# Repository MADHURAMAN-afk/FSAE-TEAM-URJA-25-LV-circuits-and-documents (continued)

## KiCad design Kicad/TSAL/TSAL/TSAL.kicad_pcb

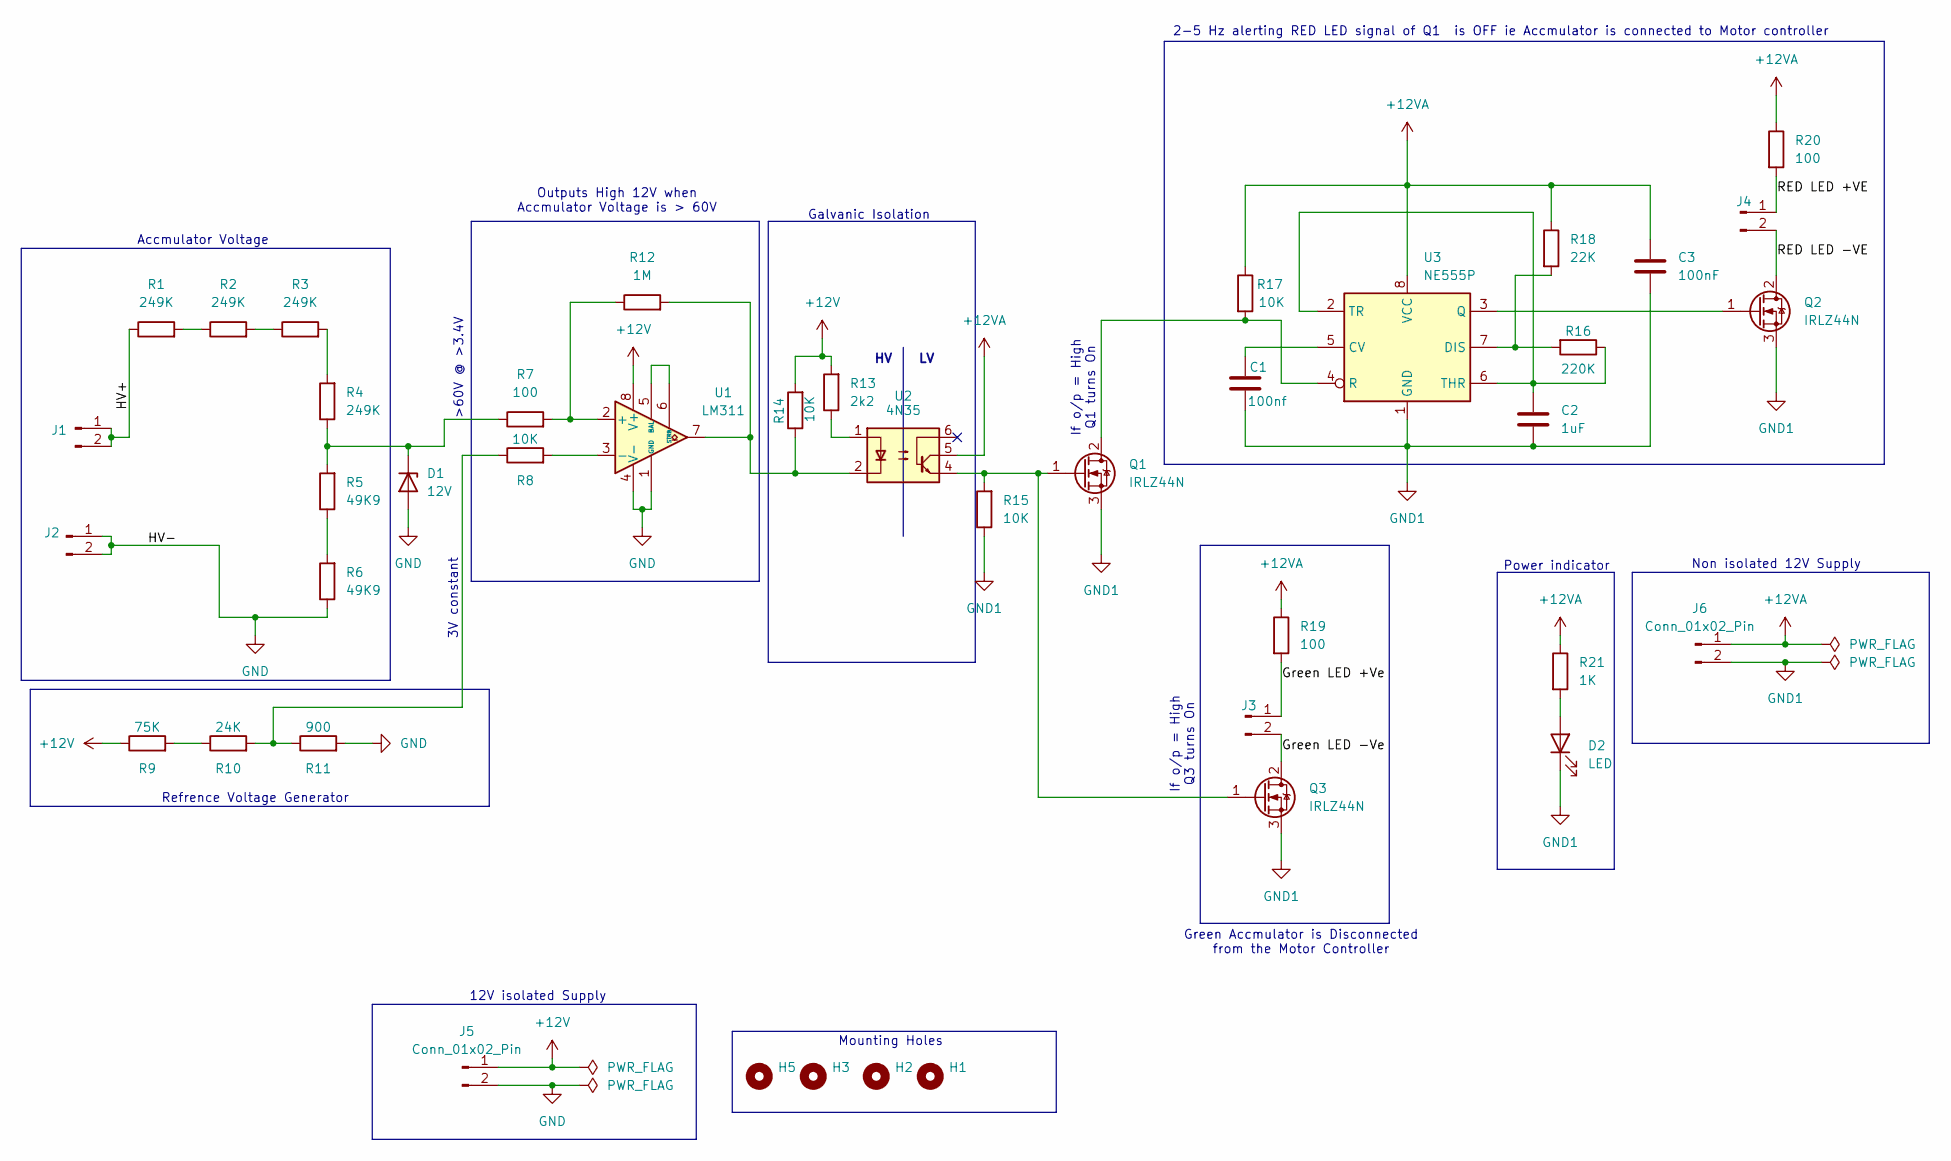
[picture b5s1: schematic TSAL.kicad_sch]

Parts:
C1: 100nf; CP_Radial_D10.0mm_P5.00mm
C2: 1uF; CP_Radial_D10.0mm_P5.00mm
C3: 100nF; CP_Radial_D10.0mm_P5.00mm
D1: 12V; D_A-405_P7.62mm_Horizontal
D2: LED; LED_D5.0mm
H1, H2, H3, H5: MountingHole; MountingHole_4.3mm_M4
J1: HV +; TerminalBlock_Phoenix_MKDS-1,5-2-5.08_1x02_P5.08mm_Horizont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
J2, J3, J4, J5, J6: Conn_01x02_Pin; TerminalBlock_Phoenix_MKDS-1,5-2-5.08_1x02_P5.08mm_Horizont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
Q1, Q2, Q3: IRLZ44N; TO-220-3_Vertical
R1, R2, R3, R4: 249K; R_Axial_DIN0207_L6.3mm_D2.5mm_P7.62mm_Horizontal
R5, R6: 49K9; R_Axial_DIN0207_L6.3mm_D2.5mm_P7.62mm_Horizontal
R7, R19, R20: 100; R_Axial_DIN0207_L6.3mm_D2.5mm_P7.62mm_Horizontal
R8, R14, R15, R17: 10K; R_Axial_DIN0207_L6.3mm_D2.5mm_P7.62mm_Horizontal
R9: 75K; R_Axial_DIN0207_L6.3mm_D2.5mm_P7.62mm_Horizontal
R10: 24K; R_Axial_DIN0207_L6.3mm_D2.5mm_P7.62mm_Horizontal
R11: 900; R_Axial_DIN0207_L6.3mm_D2.5mm_P7.62mm_Horizontal
R12: 1M; R_Axial_DIN0207_L6.3mm_D2.5mm_P7.62mm_Horizontal
R13: 2k2; R_Axial_DIN0207_L6.3mm_D2.5mm_P7.62mm_Horizontal
R16: 220K; R_Axial_DIN0207_L6.3mm_D2.5mm_P7.62mm_Horizontal
R18: 22K; R_Axial_DIN0207_L6.3mm_D2.5mm_P7.62mm_Horizontal
R21: 1K; R_Axial_DIN0207_L6.3mm_D2.5mm_P7.62mm_Horizontal
U1: LM311; CERDIP-8_W7.62mm_SideBrazed
U2: 4N35; DIP-6_W7.62mm
U3: NE555P; DIP-8_W7.62mm

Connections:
+12V: J5.1, R9.1, R13.2, R14.2, U1.8 (V+)
+12VA: C3.1, J6.1, R17.1, R18.1, R19.1, R20.1, R21.1, U2.5, U3.8 (VCC)
/Green LED +Ve: J3.1, R19.2
/Green LED -Ve: J3.2, Q3.2 (D)
/RED LED +VE: J4.1, R20.2
/RED LED -VE: J4.2, Q2.2 (D)
GND1: C1.2, C2.2, C3.2, D2.1 (K), J6.2, Q1.3 (S), Q2.3 (S), Q3.3 (S), R15.1, U3.1 (GND)
HV +VE: J1.1, J1.2, R1.1
HV -VE: D1.2 (A), J2.1, J2.2, J5.2, R6.1, R11.2, U1.1 (GND), U1.4 (V-)
unnamed: D1.1 (K), R4.1, R5.2, R7.1
unnamed: D2.2 (A), R21.2
unnamed: Q1.2 (D), R17.2, U3.4 (R)
unnamed: Q1.1 (G), Q3.1 (G), R15.2, U2.4
unnamed: Q2.1 (G), U3.3 (Q)
unnamed: R1.2, R2.1
unnamed: R2.2, R3.1
unnamed: R3.2, R4.2
unnamed: R5.1, R6.2
unnamed: R9.2, R10.1
unnamed: R8.1, R10.2, R11.1
unnamed: R12.2, R14.1, U1.7, U2.2
unnamed: R13.1, U2.1
unnamed: R7.2, R12.1, U1.2 (+)
unnamed: R8.2, U1.3 (-)
unnamed: U1.5 (BAL), U1.6 (STRB)
unnamed: C1.1, U3.5 (CV)
unnamed: R16.2, R18.2, U3.7 (DIS)
unnamed: C2.1, R16.1, U3.2 (TR), U3.6 (THR)

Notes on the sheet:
2-5 Hz alerting RED LED signal of Q1 is OFF ie Accmulator is connected to Motor controller
>60V @ >3.4V
If o/p = High Q3 turns On
Accmulator Voltage
If o/p = High Q1 turns On
Outputs High 12V when Accmulator Voltage is > 60V
Galvanic Isolation
3V constant
Mounting Holes
Non isolated 12V Supply
Refrence Voltage Generator
Power indicator
12V isolated Supply
Green Accmulator is Disconnected from the Motor Controller

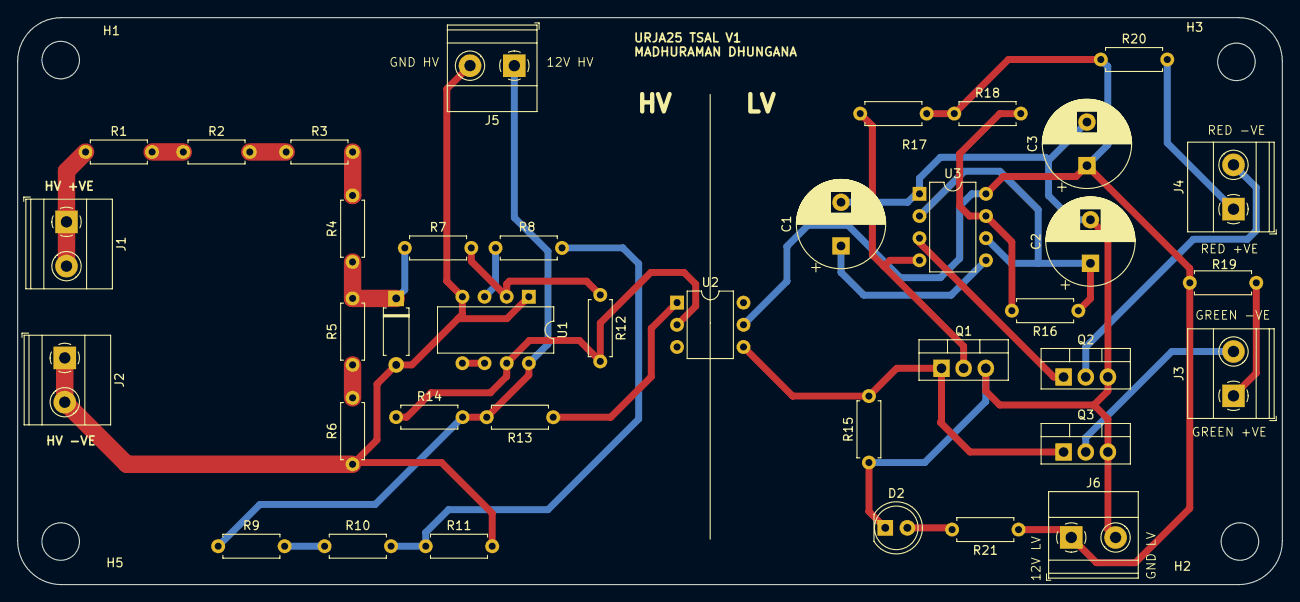
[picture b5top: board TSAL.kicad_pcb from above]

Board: 2 copper layers, 145.0 x 65.0 mm, 42 parts (0 on the bottom side), 28 nets.

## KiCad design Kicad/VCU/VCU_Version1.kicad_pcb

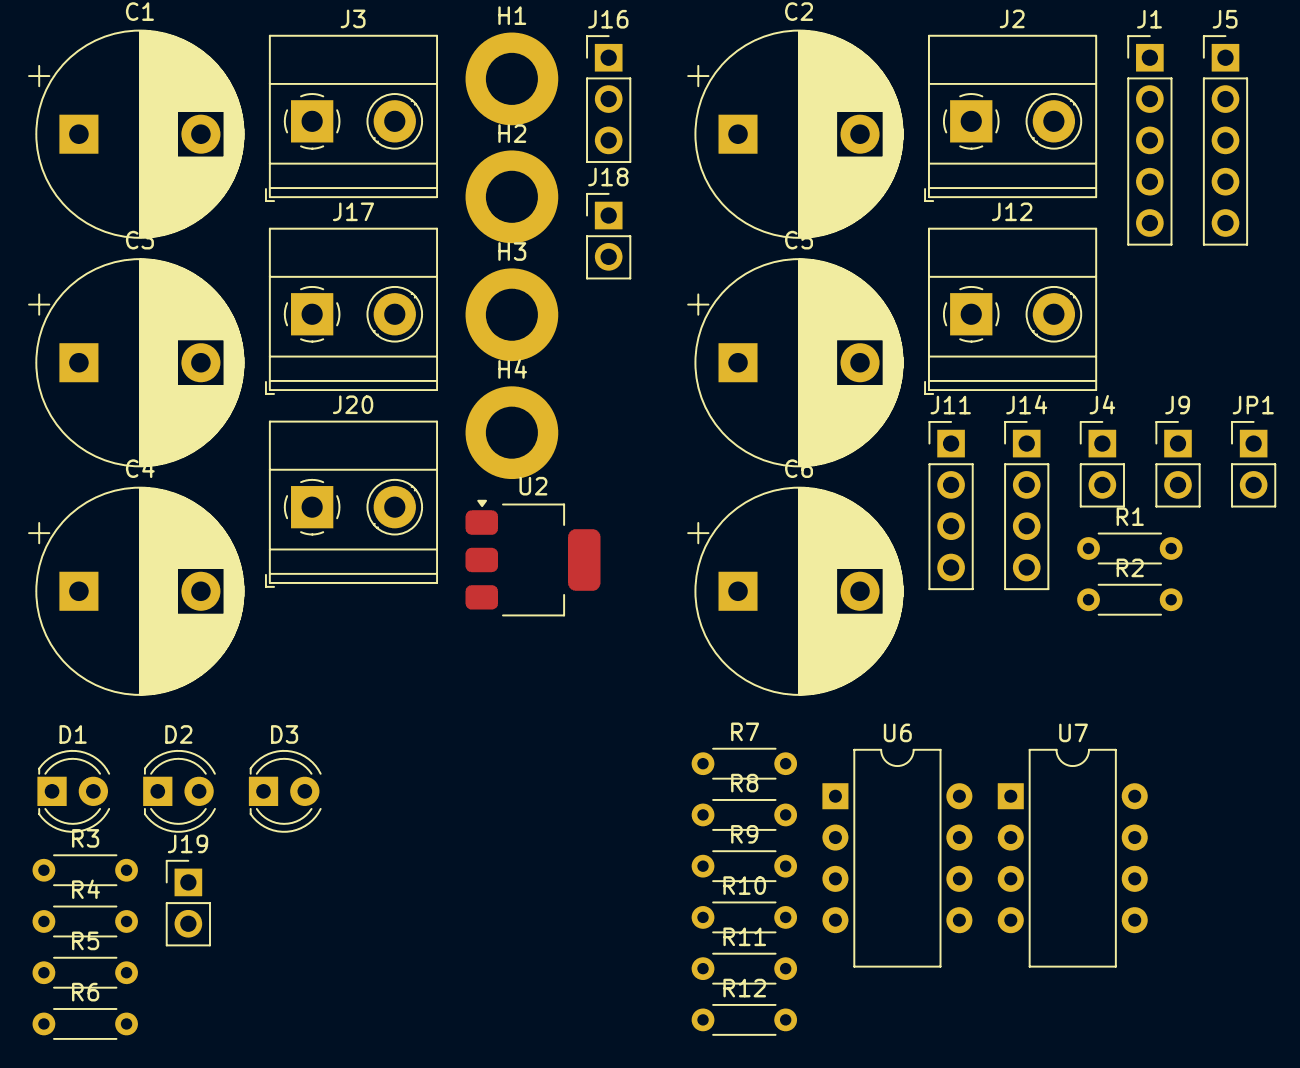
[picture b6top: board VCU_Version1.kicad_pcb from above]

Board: 2 copper layers, 43 parts (0 on the bottom side), 25 nets, no tracks yet.

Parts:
C1, C2, C3, C4, C5, C6: C; CP_Radial_D12.5mm_P7.50mm
D1, D2, D3: D; LED_D4.0mm
H1, H2, H3, H4: MountingHole_Pad; MountingHole_3.2mm_M3_ISO7380_Pad
J1, J5: Conn_01x05_Pin; PinHeader_1x05_P2.54mm_Vertical
J2, J12: Conn_01x02_Pin; TerminalBlock_Phoenix_MKDS-1,5-2-5.08_1x02_P5.08mm_Horizont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
J3, J17, J20: Screw_Terminal_01x02; TerminalBlock_Phoenix_MKDS-1,5-2-5.08_1x02_P5.08mm_Horizont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
J4, J9, J18, J19: Conn_01x02_Pin; PinHeader_1x02_P2.54mm_Vertical
J11, J14: Conn_01x04_Pin; PinHeader_1x04_P2.54mm_Vertical
J16: Conn_01x03_Pin; PinHeader_1x03_P2.54mm_Vertical
JP1: SolderJumper_2_Open; PinHeader_1x02_P2.54mm_Vertical
R1, R2: R_Small; R_Axial_DIN0204_L3.6mm_D1.6mm_P5.08mm_Horizontal
R3, R4, R5, R6, R7, R8, R9, R10, R11, R12: R; R_Axial_DIN0204_L3.6mm_D1.6mm_P5.08mm_Horizontal
U2: TLV76133DCY; SOT-223-3_TabPin2
U6, U7: LM741; CERDIP-8_W7.62mm_SideBrazed

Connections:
3V3: JP1.2 (B), R3.2
5V: C4.1, J20.2
+5V: C2.2, C6.1, J16.3
+5VA: C1.1, J17.2, U2.3 (VI)
+12V: J16.1, U6.7 (V+), U7.7 (V+)
Brake_Light_Digital: J5.4, R6.1
Free_GPIO1_AIR_Status: U7.2 (-), U7.6
Free_GPIO1_AIR_Status_In: J9.2, R10.1
GND: C2.1, C4.2, C5.1, C6.2, D1.1 (K), D2.1 (K), D3.1 (K), H1.1, H2.1, H3.1, H4.1, J3.1, J12.1, J20.1, R8.2, R11.2, U6.4 (V-), U7.4 (V-)
GNDA: C1.2, C3.2, J17.1, U2.1 (GND)
unnamed: D1.2 (A), R4.2
unnamed: D2.2 (A), R5.2
unnamed: D3.2 (A), R6.2
unnamed: J3.2, J16.2
unnamed: C3.1, J18.1, U2.2 (VO)
unnamed: J19.2, R3.1
unnamed: JP1.1 (A), R1.1, R2.1
unnamed: R7.2, R8.1, R9.1
unnamed: R10.2, R11.1, R12.1
unnamed: R9.2, U6.3 (+)
unnamed: R12.2, U7.3 (+)
RTD_Buzzer_Digital: J5.5, R4.1
SDC_O/P_DIGITAL: J5.3, R5.1
SDC_Status_In: J1.4, R7.1
SDC_Status_In_VCU: U6.2 (-), U6.6
